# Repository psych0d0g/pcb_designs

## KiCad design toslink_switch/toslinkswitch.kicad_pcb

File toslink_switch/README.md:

This project consists of KiCAD files and sourcecode for the shown PCB:

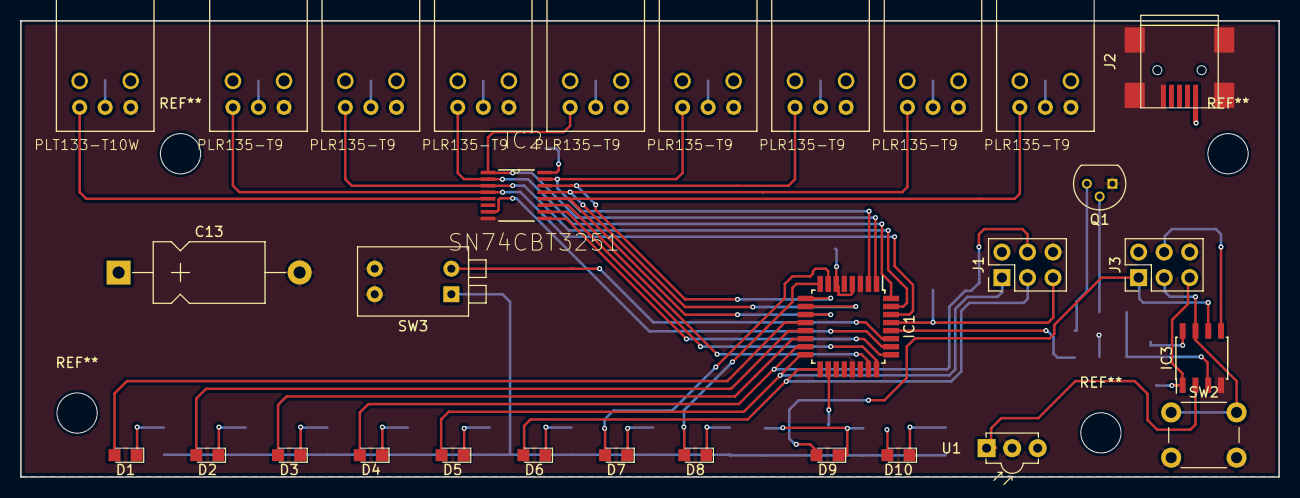
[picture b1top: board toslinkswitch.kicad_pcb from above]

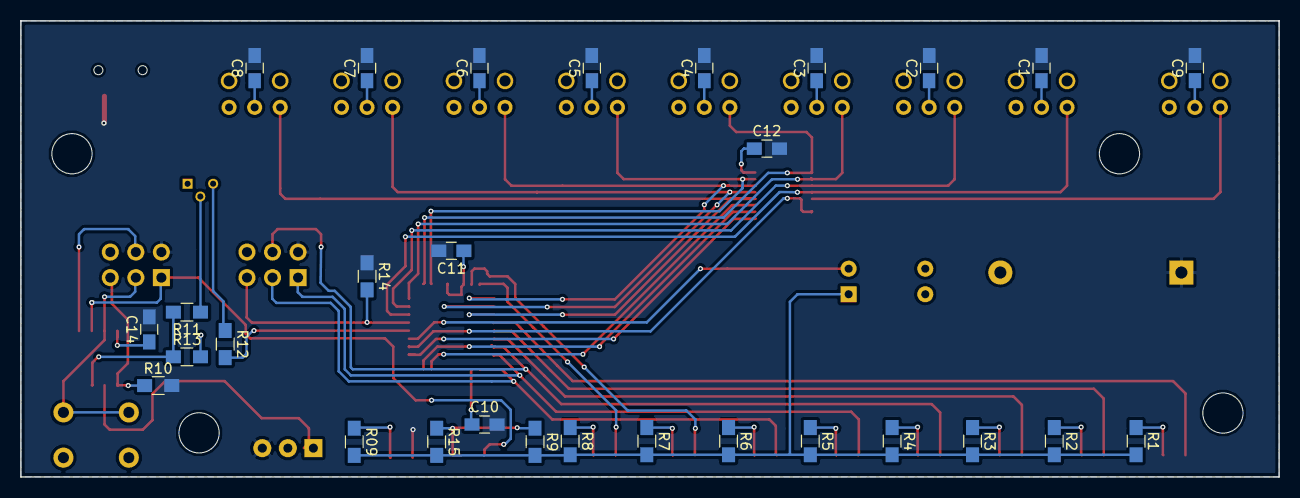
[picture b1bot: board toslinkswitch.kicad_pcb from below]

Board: 2 copper layers, 125.1 x 45.3 mm, 59 parts (29 on the bottom side), 58 nets.

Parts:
C1, C2, C3, C4, C5, C6, C7, C8, C9, C10, C11, C14: 100n; C_0805_HandSoldering
C12: n100; C_0805_HandSoldering
C13: 100u; CP_Axial_L11.0mm_D6.0mm_P18.00mm_Horizontal
D1, D2, D3, D4, D5, D6, D7, D8, D9, D10: LED; LED_0805
IC1: ATMEGA48A-AU; TQFP-32_7x7mm_Pitch0.8mm
IC2: SN74CBT3251; SOP65P640X120-16N
IC3: ATTINY85-20SU; SOIC-8_3.9x4.9mm_Pitch1.27mm
IN1, IN2, IN3, IN4, IN5, IN6, IN7, IN8: PLR135-T9; PLT133-T10W
J1, J3: CONN_02X03; Pin_Header_Straight_2x03_Pitch2.54mm
J2: USB_OTG; USB_Mini-B
OUT1: PLT133-T10W
Q1: PN2222A; TO-92_Molded_Narrow
R1, R2, R3, R4, R5, R6, R7, R8, R9, R09, R15: 330; R_0805_HandSoldering
R10, R14: 10k; R_0805_HandSoldering
R11, R12: 47; R_0805_HandSoldering
R13: 1k; R_0805_HandSoldering
SW2: INPUT_CYCL_SW; SW_PUSH_6mm_h4.3mm
SW3: SW_DIP_x02; SW_DIP_x2_W7.62mm_Piano
U1: TSOP382xx; IRReceiver_Vishay_MINICAST-3pin

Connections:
/OE: IC1.26, IC2.7
CYCLSW: IC1.28, R12.2
DIP1: R1.2, R2.2, R3.2, R4.2, R5.2, R6.2, R7.2, R8.2, R9.2, R09.2, R15.2, SW3.1
DIP2: IC1.27, SW3.2
GND: C13.2, IC1.3, IC1.5, IC1.21, IC2.8, IC3.4, IN1.1, IN2.1, IN3.1, IN4.1, IN5.1, IN6.1, IN7.1, IN8.1, J1.6, J2.5, J2.6, J3.6, OUT1.1, Q1.1, R13.2, SW2.2, SW3.3, SW3.4, U1.2
IN1: IC1.30, IC2.4, IN1.3
IN2: IC1.31, IC2.3, IN2.3
IN3: IC1.32, IC2.2, IN3.3
IN4: IC1.1, IC2.1, IN4.3
IN5: IC1.2, IC2.15, IN5.3
IN6: IC1.9, IC2.14, IN6.3
IN7: IC1.10, IC2.13, IN7.3
IN8: IC1.11, IC2.12, IN8.3
IR: IC3.2, U1.1
IRSWSIG: IC3.3, R11.2, R13.1
LED1: D1.2, IC1.12
LED2: D2.2, IC1.13
LED3: D3.2, IC1.14
LED4: D4.2, IC1.15, J1.4
LED5: D5.2, IC1.16, J1.1
LED6: D6.2, IC1.17, J1.3
LED7: D7.2, IC1.7
LED8: D8.2, IC1.8
LED9: D9.2, IC3.6, J3.1
unnamed: C1.1, IN1.2
unnamed: C2.1, IN2.2
unnamed: C3.1, IN3.2
unnamed: C4.1, IN4.2
unnamed: C5.1, IN5.2
unnamed: C6.1, IN6.2
unnamed: C7.1, IN7.2
unnamed: C8.1, IN8.2
unnamed: C9.1, OUT1.2
unnamed: C10.1, IC1.18
unnamed: C11.1, IC1.4, IC1.6
unnamed: C12.1, IC2.16
unnamed: C14.1, IC3.8
unnamed: D1.1, R1.1
unnamed: D2.1, R2.1
unnamed: D3.1, R3.1
unnamed: D4.1, R4.1
unnamed: D5.1, R5.1
unnamed: D6.1, R6.1
unnamed: D7.1, R7.1
unnamed: D8.1, R8.1
unnamed: D9.1, R9.1, R15.1
unnamed: D10.1, R09.1
unnamed: IC1.29, J1.5, R14.2
unnamed: IC3.1, J3.5, R10.1
unnamed: IC3.5, J3.4
unnamed: Q1.2, R11.1
unnamed: Q1.3, R12.1
OUT: IC2.5, OUT1.3
S0: IC1.23, IC2.11
S1: IC1.24, IC2.10
S2: IC1.25, IC2.9
TACT: IC3.7, J3.3, SW2.1
VCC: C1.2, C2.2, C3.2, C4.2, C5.2, C6.2, C7.2, C8.2, C9.2, C10.2, C11.2, C12.2, C13.1, C14.2, D10.2, J1.2, J2.1, J3.2, R10.2, R14.1, U1.3

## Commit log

2017-04-03 move into subfolder
2017-04-03 cleanup the project files
2017-04-03 add preview image of the current layout
2017-04-03 add attiny for IR reciver functionality (https://blog.turboturbo.net/2016/10/01/ir-pc-power-on-quick-n-dirty/)
2017-04-03 add needed library to compile attiny IR firmware
2017-04-03 move readme to sourcecode dir
2017-04-03 restructure firmware directory to make clear which firmware is for which ic
2017-04-03 put a link to where the download of the atmega firmware is found
2017-04-03 tell people where they can download the atmega firmware
2017-04-03 add a small initial readme
2017-04-03 put some mounting holes where we still have space, we can cleanup later
2017-04-03 update pcb image
2017-04-03 small tweaks to ic3 location
2017-04-03 Structurized the Schematics to better get a grip on the components
2017-04-04 move led's close to the edge of the board
2017-04-11 added ir indicator LED, rewrired tact switch to attiny instead of atmega, attiny will handle manual switching from now on. tact switch will provide manual switching on short press and IR code learnin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
